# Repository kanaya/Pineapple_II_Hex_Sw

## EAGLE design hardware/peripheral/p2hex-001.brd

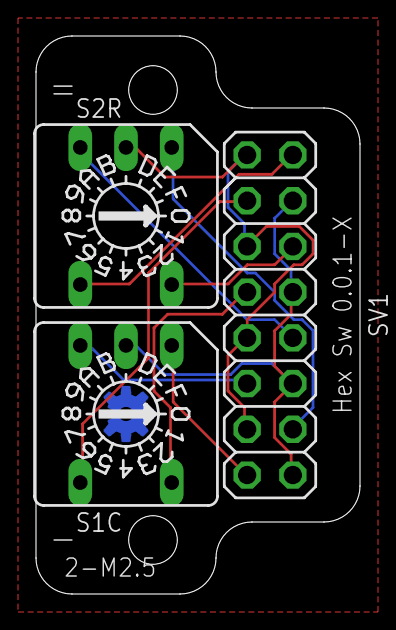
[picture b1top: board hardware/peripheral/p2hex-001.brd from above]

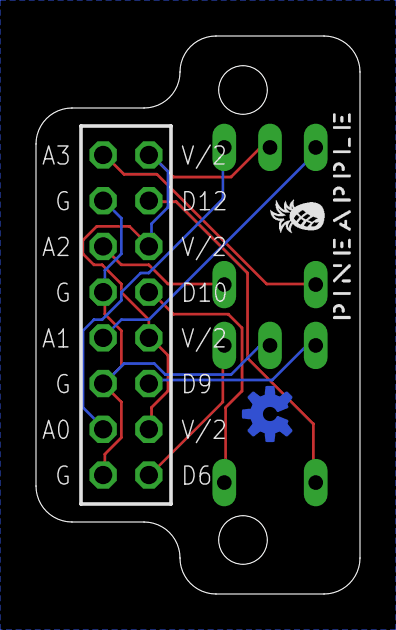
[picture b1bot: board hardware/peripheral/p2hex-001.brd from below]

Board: 2 copper layers, 18.0 x 31.0 mm, 5 parts (2 on the bottom side), 10 nets.

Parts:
LOGO1: OSHW-LOGOS-COPPER; OSHW-LOGO-S_COPPER
S1C, S2R: A1353HEX
SV1: 2X08
U$1: PINEAPPLE450_SILK

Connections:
ANLG0: S2R.1, SV1.3
ANLG1: S2R.4, SV1.7
ANLG2: S2R.8, SV1.11
ANLG3: S2R.2, SV1.15
DTCT0: S1C.1, SV1.2
DTCT1: S1C.4, SV1.6
DTCT2: S1C.8, SV1.10
DTCT3: S1C.2, SV1.14
GND: S1C.C, SV1.1, SV1.5, SV1.9, SV1.13
VCC: S2R.C, SV1.4, SV1.8, SV1.12, SV1.16

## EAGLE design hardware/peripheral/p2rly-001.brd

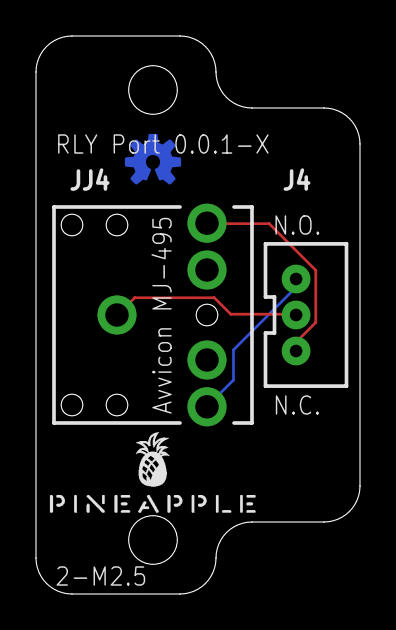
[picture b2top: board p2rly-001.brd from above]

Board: 2 copper layers, 18.0 x 31.0 mm, 4 parts (1 on the bottom side), 3 nets.

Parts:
J4: RLY; JST-3-PTH-VERT
JJ4: AUDIO_JACK_3.5MM_KIT; AUDIO-JACK-KIT
LOGO1: OSHW-LOGOS-COPPER; OSHW-LOGO-S_COPPER
U$1: PINEAPPLE450_SILK

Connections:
COMMON: J4.2, JJ4.SLEEVE
NC: J4.3, JJ4.RING
NO: J4.1, JJ4.TIP

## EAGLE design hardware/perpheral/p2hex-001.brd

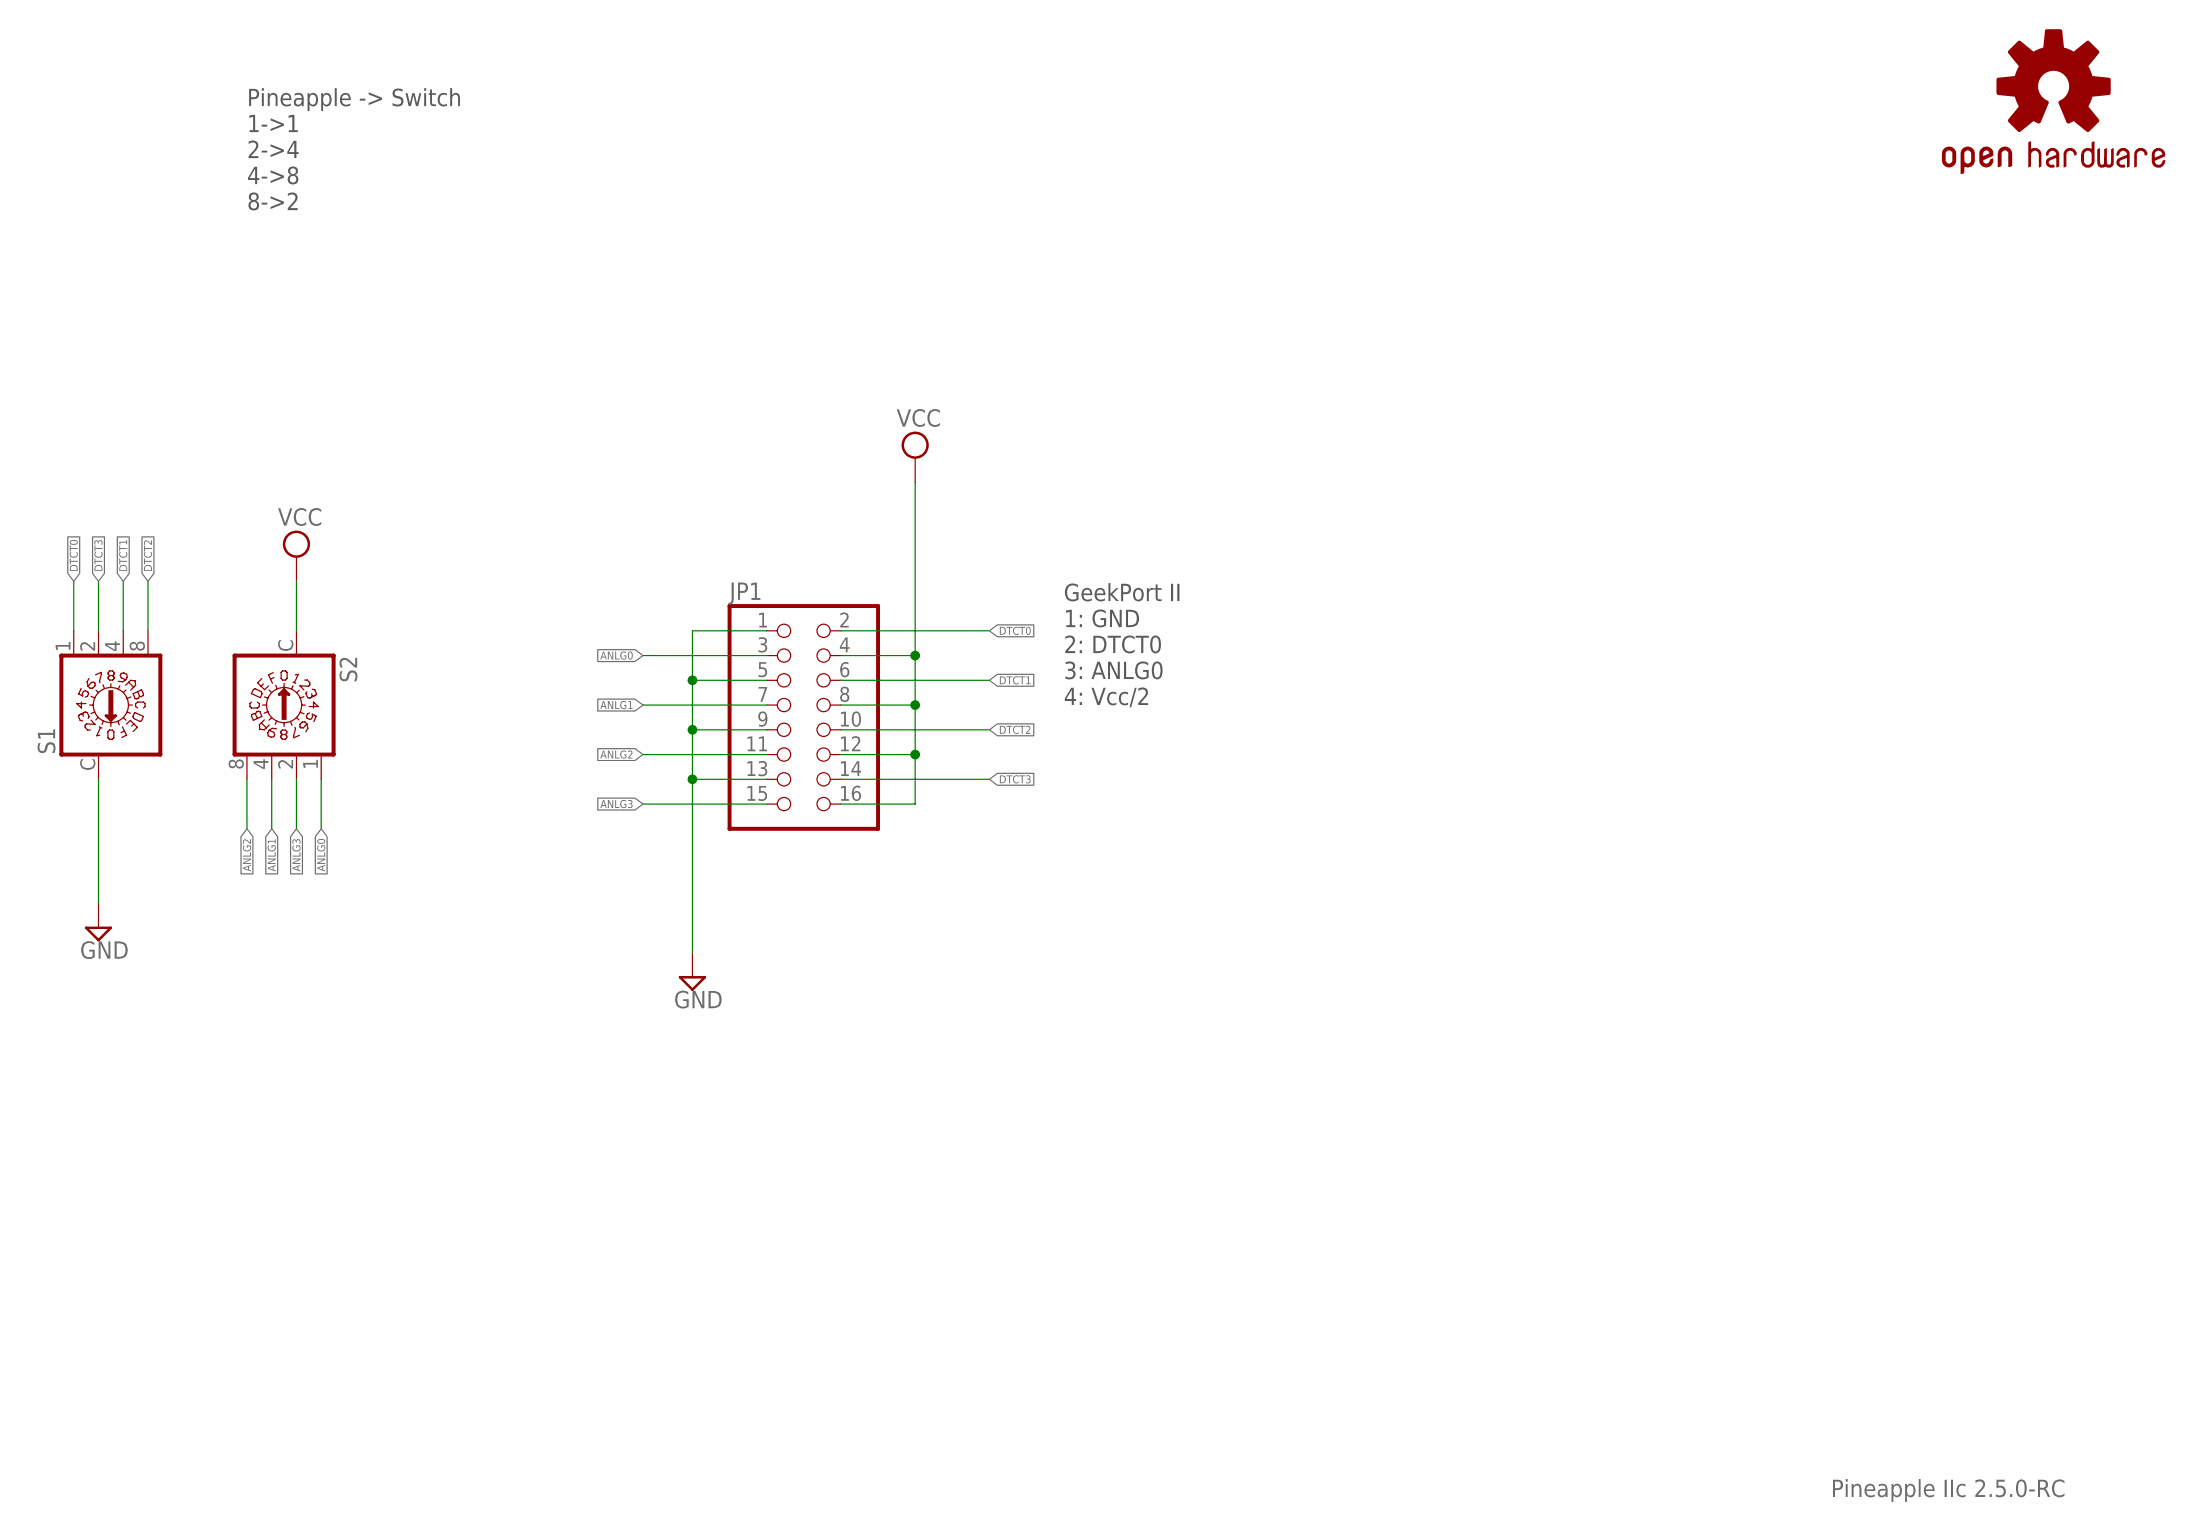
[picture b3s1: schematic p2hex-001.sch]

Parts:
JP1: PINHD-2X8; 2X08
LOGO1: OSHW-LOGOS-COPPER; OSHW-LOGO-S_COPPER
S1, S2: A1353HEX

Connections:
ANLG0: JP1.3, S2.1
ANLG1: JP1.7, S2.4
ANLG2: JP1.11, S2.8
ANLG3: JP1.15, S2.2
DTCT0: JP1.2, S1.1
DTCT1: JP1.6, S1.4
DTCT2: JP1.10, S1.8
DTCT3: JP1.14, S1.2
GND: JP1.1, JP1.5, JP1.9, JP1.13, S1.C
VCC: JP1.4, JP1.8, JP1.12, JP1.16, S2.C

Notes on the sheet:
Pineapple IIc 2.5.0-RC
Pineapple -> Switch 1->1 2->4 4->8 8->2
GeekPort II 1: GND 2: DTCT0 3: ANLG0 4: Vcc/2

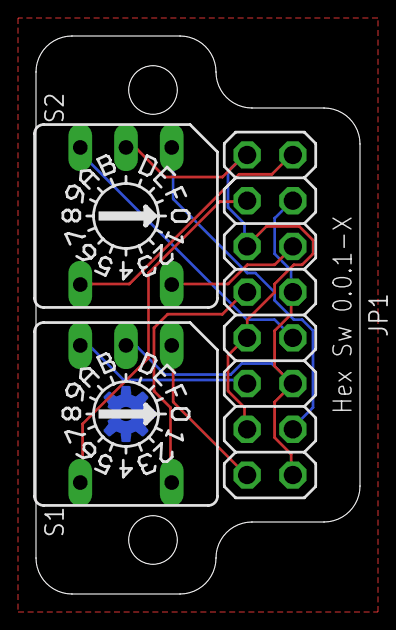
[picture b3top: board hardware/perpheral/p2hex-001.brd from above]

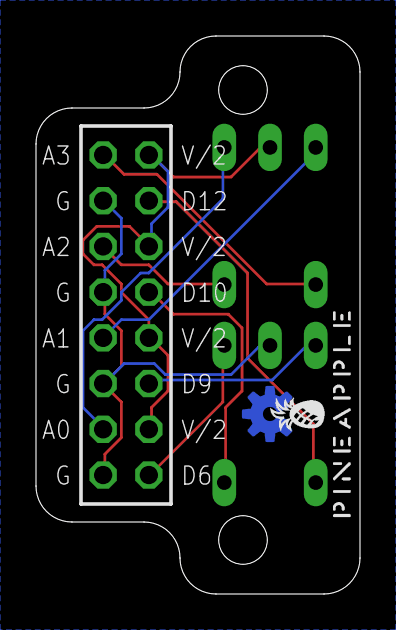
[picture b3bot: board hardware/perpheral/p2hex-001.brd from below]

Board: 2 copper layers, 18.0 x 31.0 mm, 5 parts (2 on the bottom side), 10 nets.

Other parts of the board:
U$1: PINEAPPLE450_SILK

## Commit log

2021-12-01 Copied parts from Pineapple IIc 2.5.0-RC.
2021-12-01 First try.
2021-12-01 Second try.
2021-12-19 Moved Pineapple logo.
2022-02-19 Rename of directory.
2022-03-09 Silk.
2022-08-15 Copied HEXSW to RLY.
2022-08-15 Relay port.
2022-08-15 Symbol name.
2022-08-16 Removed Pineapple II RLY Port. (They are now moved to Pineapple_II_RLY_Port.)

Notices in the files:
parts and their libraries:
SparkFun-Aesthetics: Licensing: Creative Commons ShareAlike 4.0 International - https://creativecommons.org/licenses/by-sa/4.0
